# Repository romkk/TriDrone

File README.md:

## About

Firmware and software collection of project "TriDrone".
It is a micro-copter project.

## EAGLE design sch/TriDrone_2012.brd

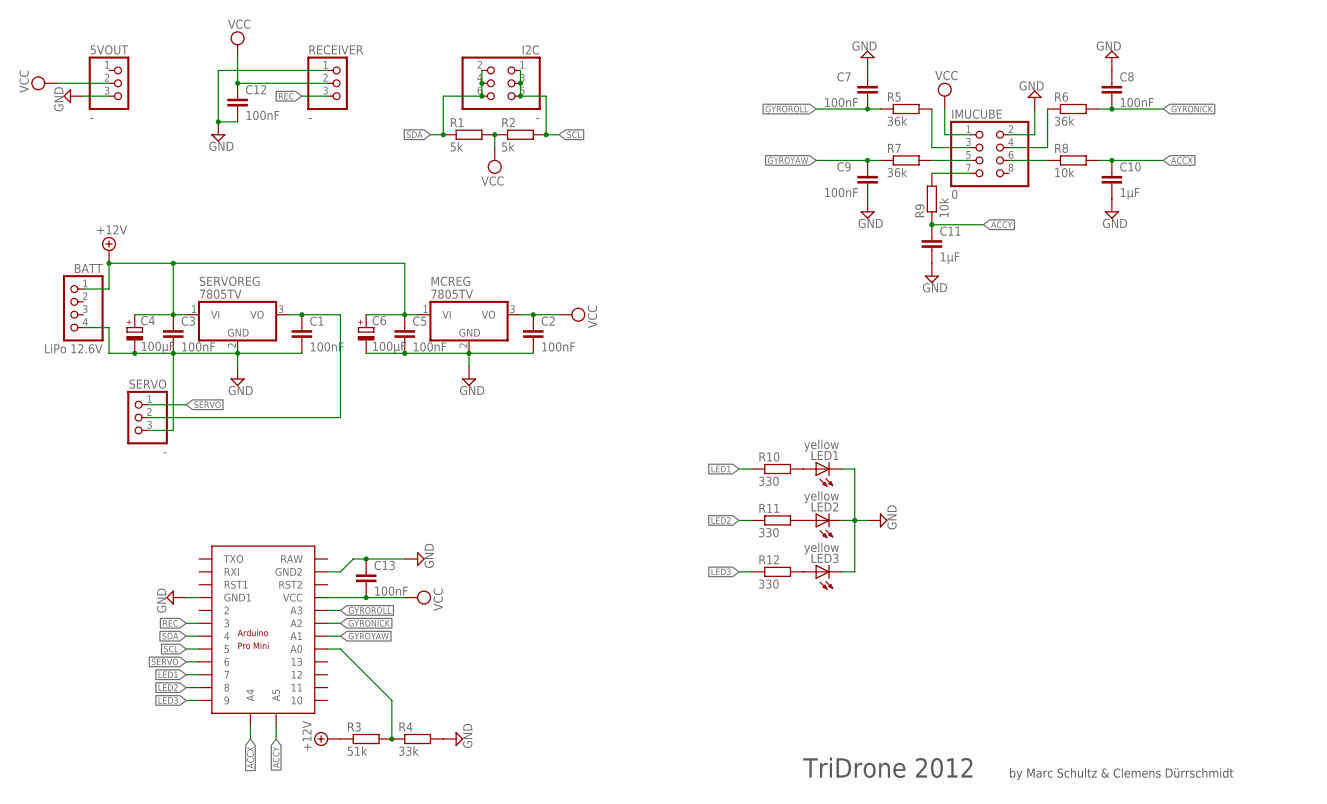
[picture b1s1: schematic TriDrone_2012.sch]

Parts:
5VOUT: -; 1X03
BATT: LiPo 12.6V; 1X04/90
C1, C2, C3, C5, C7, C8, C9, C12, C13: 100nF; C025-025X050
C4, C6: 100µF; E2,5-7
C10, C11: 1µF; C025-025X050
I2C: -; 2X03/90
IMUCUBE: 0; 2X04
LED1, LED2, LED3: yellow; LED3MM
MCREG: 7805TV; TO220V
R1, R2: 5k; 0204/7
R3: 51k; 0204/7
R4: 33k; 0204/7
R5, R6, R7: 36k; 0204/7
R8, R9: 10k; 0204/7
R10, R11, R12: 330; 0204/7
RECEIVER: -; 1X03
SERVO: -; 1X03
SERVOREG: 7805TV; TO220V
U$2: ARDUINO_PRO_MINI

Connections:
+12V: BATT.1, C3.1, C4.+, C5.1, C6.+, MCREG.1 (VI), R3.1, SERVOREG.1 (VI)
ACCX: C10.1, R8.2, U$2.A4
ACCY: C11.1, R9.1, U$2.A5
GND: 5VOUT.3, BATT.4, C1.2, C2.2, C3.2, C4.-, C5.2, C6.-, C7.1, C8.1, C9.2, C10.2, C11.2, C12.2, C13.1, IMUCUBE.2, LED1.K (C), LED2.K (C), LED3.K (C), MCREG.2 (GND), R4.2, RECEIVER.1, SERVO.3, SERVOREG.2 (GND), U$2.GND1, U$2.GND2
GYRONICK: C8.2, R6.2, U$2.A2
GYROROLL: C7.2, R5.1, U$2.A3
GYROYAW: C9.1, R7.1, U$2.A1
LED1: R10.1, U$2.7
LED2: R11.1, U$2.8
LED3: R12.1, U$2.9
unnamed: IMUCUBE.3, R5.2
unnamed: C1.1, SERVO.2, SERVOREG.3 (VO)
unnamed: IMUCUBE.4, R6.1
unnamed: R3.2, R4.1, U$2.A0
unnamed: IMUCUBE.6, R8.1
unnamed: IMUCUBE.5, R7.2
unnamed: IMUCUBE.7, R9.2
unnamed: LED1.A, R10.2
unnamed: LED2.A, R11.2
unnamed: LED3.A, R12.2
REC: RECEIVER.3, U$2.3
SCL: I2C.1, I2C.3, I2C.5, R2.2, U$2.5
SDA: I2C.2, I2C.4, I2C.6, R1.1, U$2.4
SERVO: SERVO.1, U$2.6
VCC: 5VOUT.2, C2.1, C12.1, C13.2, IMUCUBE.1, MCREG.3 (VO), R1.2, R2.1, RECEIVER.2, U$2.VCC

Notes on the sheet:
TriDrone 2012
by Marc Schultz & Clemens Dürrschmidt

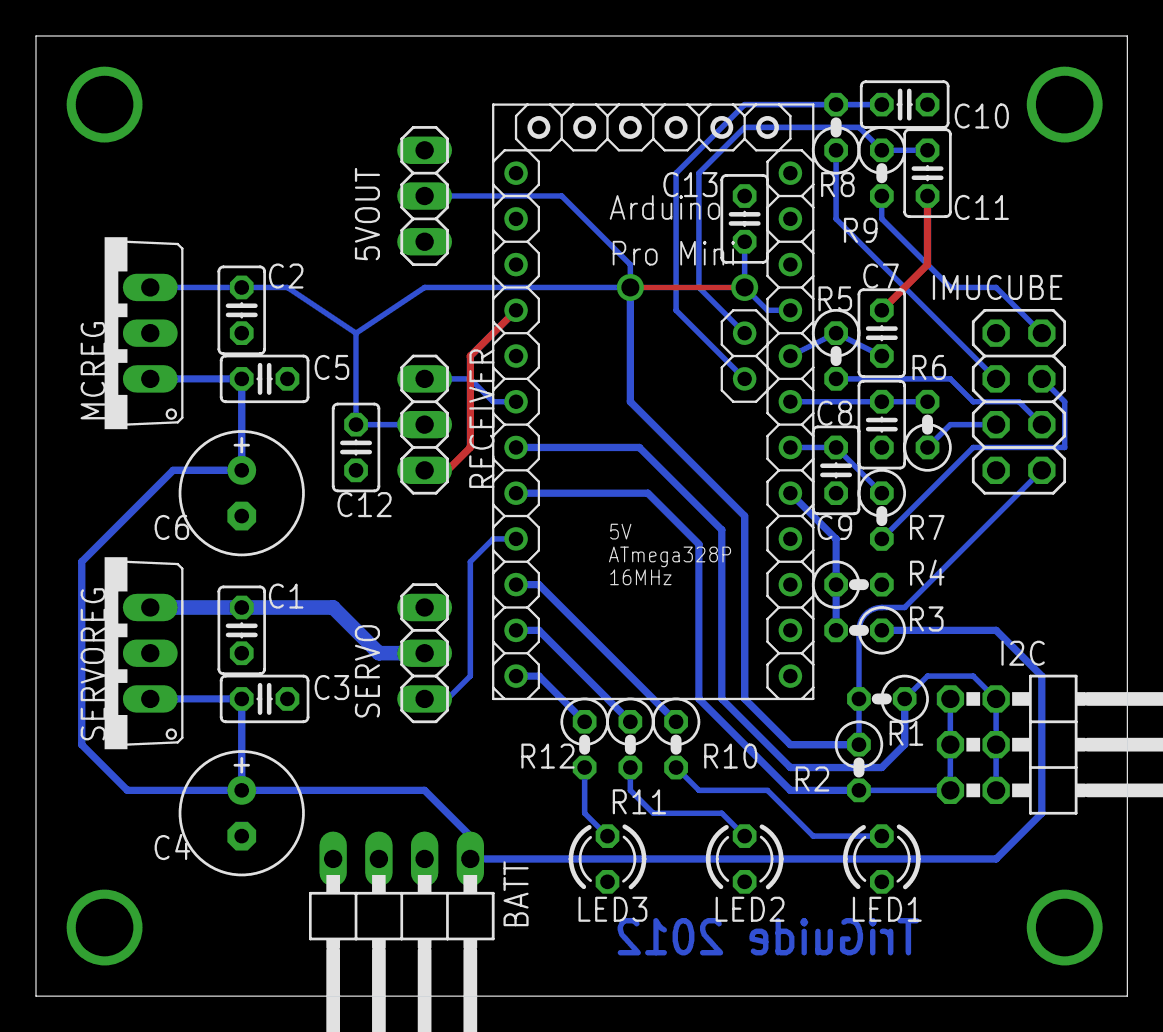
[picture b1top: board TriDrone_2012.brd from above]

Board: 2 copper layers, 60.6 x 53.3 mm, 37 parts (0 on the bottom side), 25 nets.

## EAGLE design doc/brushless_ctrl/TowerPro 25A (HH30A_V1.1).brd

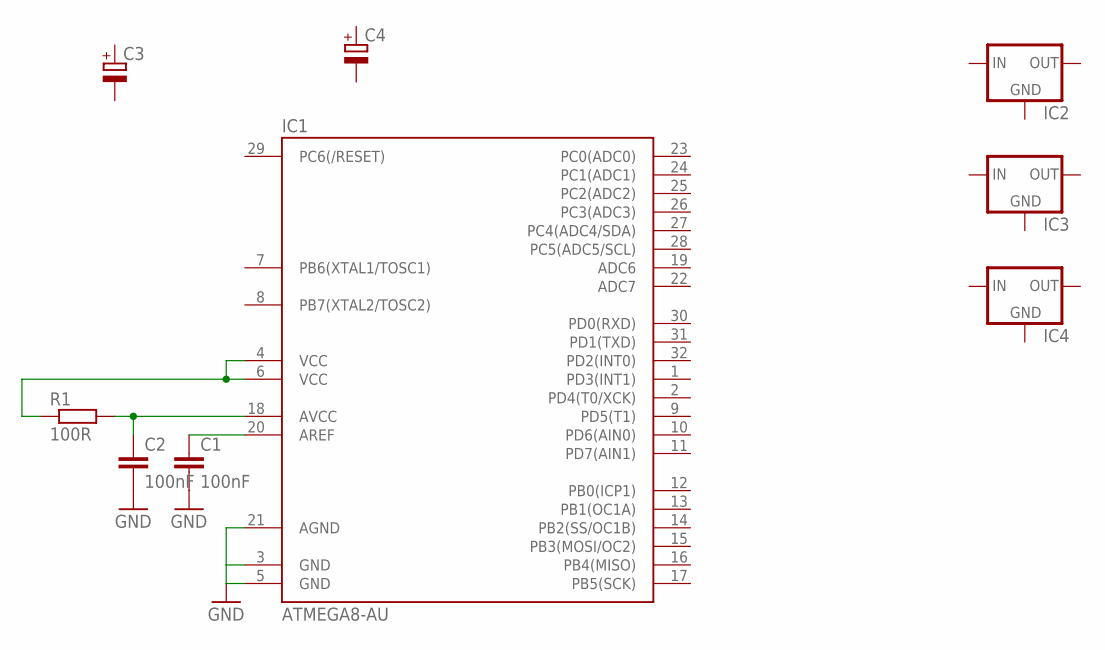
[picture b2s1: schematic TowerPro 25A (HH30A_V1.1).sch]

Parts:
C1, C2: 100nF; C2.5-3
C3, C4: CPOL-EUE3.5-10; E3,5-10
IC1: ATMEGA8-AU; TQFP32-08
IC2, IC3, IC4: 78MXXL
R1: 100R; M1206

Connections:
GND: C1.2, C2.2, IC1.3 (GND), IC1.5 (GND), IC1.21 (AGND)
unnamed: C1.1, IC1.20 (AREF)
unnamed: C2.1, IC1.18 (AVCC), R1.2
unnamed: IC1.4 (VCC), IC1.6 (VCC), R1.1

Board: 2 copper layers, 9 parts (0 on the bottom side), 4 nets, no tracks yet.

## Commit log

2012-08-05 ADD schematics
2012-08-05 added gui mockup
2012-08-05 ADD documentation files and datasheets
2012-08-05 cleanup
2012-08-05 UPDATE connectivity diagramm
2012-08-05 FIX location of firmware src
